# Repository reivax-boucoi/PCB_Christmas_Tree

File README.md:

# PCB_Christmas_Tree
This project is a simple PCB based Christmas ornament with blinky LEDs and rechargeable supercaps.

---
---

### Hardware

---

Project was done in Kicad (yay for open-source !). Project files are here: ```Hardware\Kicad\```, including the custom footprint library ```Hardware\Kicad\christmas_tree.pretty```.

#### Schematic

---

Schematic : ```Hardware\schematic.pdf```

Bill of Materials : ```Hardware\BOM.csv```

Components were chosen based on my current stock. 
* **Power storage**: Instead of traditional batteries, 2 Maxwell 10F 2.7V supercapacitors were used as rechargeable storage, just because I have a bunch of them and don't like non-rechargeable gadgets. Granted, I estimated the tree can only run about 1 hour max per charge (approx. 6mA average current draw), which is not great considering a single CR2032 could probably last several weeks. But, supercaps are fun and you can recharge them with any USB port in <1min.
* **Charging**: An integrated USB connector allows direct charging of the supercaps, through a current limiting resistor. Do not make it less than ~15Ω to not exceed USB spec current capabilities. I added an optional charge balancing circuitry with TL431 shunt Vref, but didn't used it in the end as my caps were quite similar in capacity.
* **Brain of the operations**: I used the ever popular Attiny 25/45/85 series, a small 8-bit AVR micro which offers more than enough capabilities & programming space than I need. Programming port is a TagConnect footprint modified to remove the through holes.
* **LEDs**: Given the limited amount of GPIOs on the µC, I turned to [Charlieplexing](https://en.wikipedia.org/wiki/Charlieplexing), which allows with some clever tricks to drive 12 LEDs with only 4 pins. One thing though, if you want to use different color LEDs you won't be able to adjust their individual brightness easily, so blue LEDs will be dimmer than red by example.
* **Touch button**: For extra fanciness I added a TTP223 touch sensor chip, which allows to cycle between different display modes. The default config works fine even if not populated.

#### Layout

---

To keep this project cheap, the goal was to fit the whole layout on a 10x10cm 2 layer board, which JLCPCB famously offers at 2$ for 5pcs. Decision was made to split the tree in 2 halves that would then be soldered back together, to get a bit extra height. 

For the 1st time I experimented with using the different layers (bare FR4 material, bare copper, copper+soldermask, bare soldermask and silkscreen) to make a somewhat artistic result. For more info on the colors you can get when playing with PCBs I would recommend visiting [this page](https://github.com/Hanqaqa/PCB_Color_Palette).

- Exposed pads spanning the 2 halves of the tree allow to join them and propagate the tracks for the LEDs
- Leds are reverse mounted so they shine through the board: solder mask keepout areas are placed on both sides to let the light through.
- Base of the tree doubles as a USB A port to easily recharge the batteries
- Supercapacitors provide mechanical support to stand the tree upright

<div style="float:left;"> 

</div> 

#### Ordering

---

Zipped gerbers are available (```Hardware\Kicad\gerbers.zip```)to be directly dropped on manufacturers websites like JLCPCB. I used their excellent prototype service for my boards, both cheap and quick.

Feel free to use these files as is or modify and improve the project. Don't forget to share our version as well!

Final dimensions are 88.7mm*98mm.

Ordering settings: 2 layers, 1.6mm board thickness, white silkscreen, HASL(with lead) surface finish, 1oz copper weight, Specify a location for Remove Order Number,

In the Remarks field: "Please note: Some parts use Solder Mask Defined Pads. Do not compensate/modify the solder mask for them. No edge plating required. Center cutout to be routed and discarded."

#### Assembly

---

<div style="float:left;"> 

</div> 
The PCB comes with the 2 halves attached with mousebites. Once separated the remaining burs can be filed off.

Minimum components to be assembled are: C1&C2 supercaps, SW1 power switch, U3 microcontroller, R1 & R10 charging resistors, the 4 220Ω resistors and the LEDs.

To avoid making a custom TagConnect to ICSP adapter, the µC can be programmed in a socket before being soldered on the board.

#### Programming

---

Precompiled version of the firmware: ```Software\main.hex```

To upload using avrdude, run the following commands : `avrdude -u -c usbtiny -p t85 -B 5 -F -U flash:w:main.hex:a -U lfuse:w:0xE2:m -U hfuse:w:0xDF:m -U efuse:w:0xFF:m`

---
---

### Software

---

Software uses Timer1 to cycle between each LED and light it using a 7 bit intensity scale. Several blinking modes can be cycled through with the touch button: fade (default), pixies and debug (one LED at a time)

```Program: TODO bytes (TODO% Full) & Data: TODO bytes (TODO% Full)```

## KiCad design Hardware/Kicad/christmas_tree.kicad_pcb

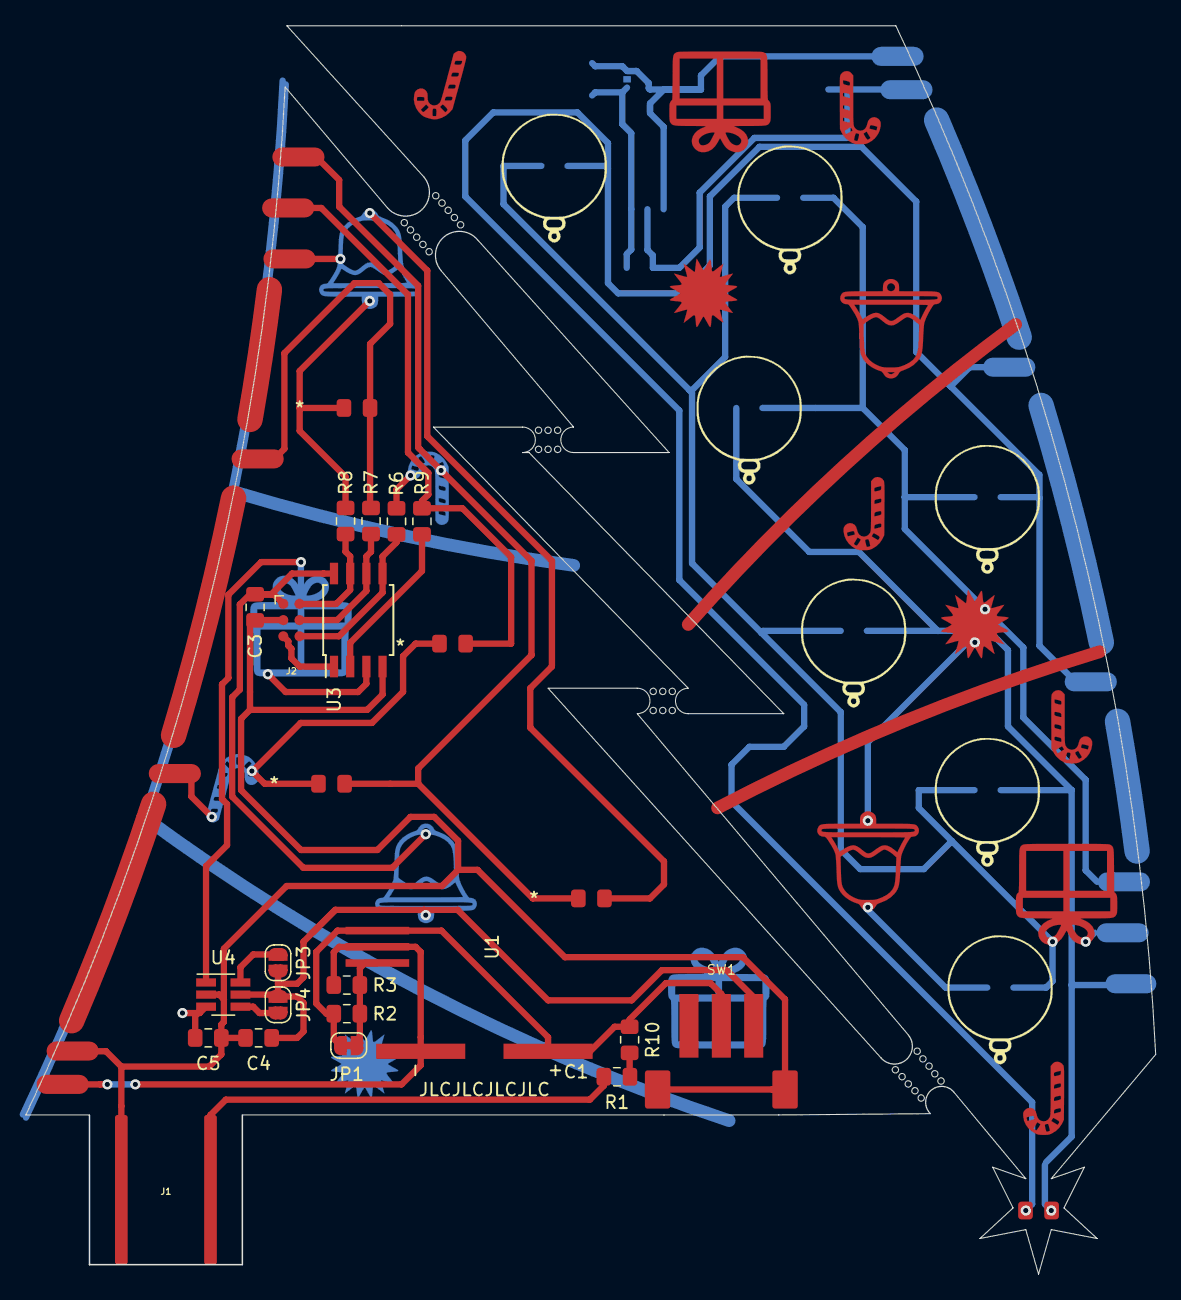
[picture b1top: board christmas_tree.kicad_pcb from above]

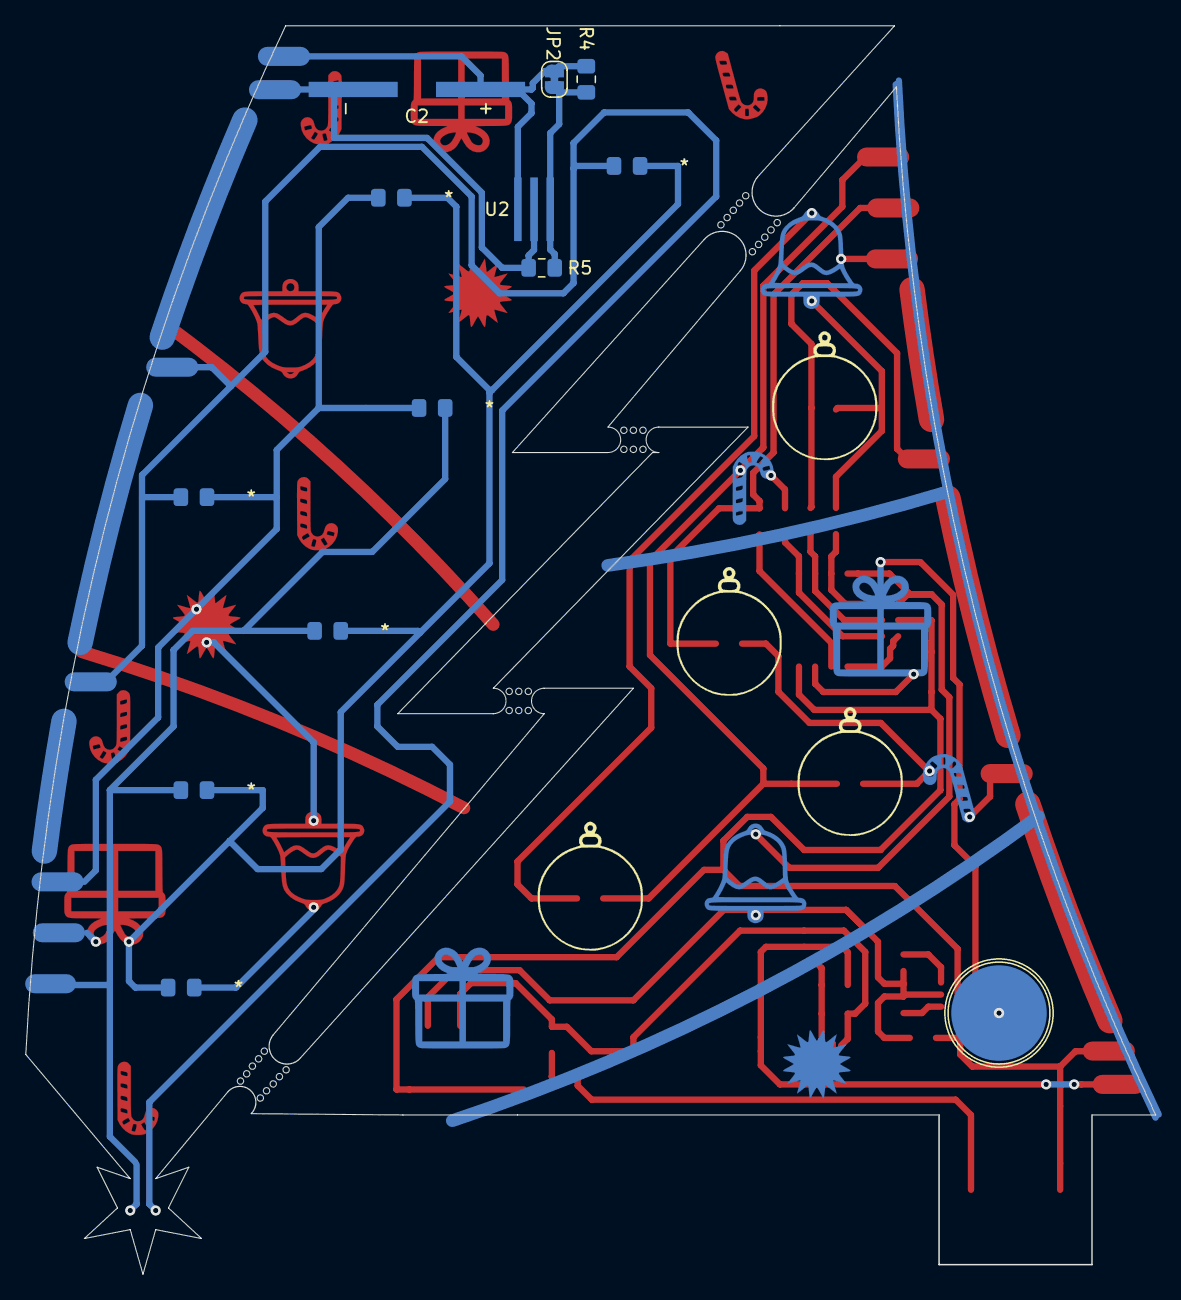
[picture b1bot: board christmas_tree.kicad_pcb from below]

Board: 2 copper layers, 88.7 x 98.0 mm, 43 parts (12 on the bottom side), 21 nets.

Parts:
C1, C2: 10F; Supercap_SMD
C3, C4: 100n; C_0805_2012Metric_Pad1.15x1.40mm_HandSolder
C5: DNP; C_0805_2012Metric_Pad1.15x1.40mm_HandSolder
D1: LED; LED_0805_2012Metric_Pad1.15x1.40mm_HandSolder
D2, D4, D5, D7: LED; LED_0805_orb_r
D3, D6, D8, D9, D10, D11, D12: LED; LED_0805_orb
J1: USB_A; USBA_PCB
J2: Conn_01x06; Tag-Connect_noHoles
J3: Touch; Touch_capacitive
JP1, JP2: Jumper_NC_Small; SolderJumper-2_P1.3mm_Bridged_RoundedPad1.0x1.5mm
JP3, JP4: Jumper_NO_Small; SolderJumper-2_P1.3mm_Open_RoundedPad1.0x1.5mm
R1, R10: 100; R_0805_2012Metric_Pad1.15x1.40mm_HandSolder
R2, R4: 12k; R_0805_2012Metric_Pad1.15x1.40mm_HandSolder
R3, R5: 280k; R_0805_2012Metric_Pad1.15x1.40mm_HandSolder
R6, R7, R8, R9: 220; R_0805_2012Metric_Pad1.15x1.40mm_HandSolder
SW1: SW_SPDT_shield; SPDT_SW_pcb_edge_mount
U1, U2: TL431LP; TO92_H
U3: ATtiny45-20SU; SOIJ-8_5.3x5.3mm_P1.27mm
U4: TTP223; SOT-23-6_Handsoldering
mouse-bite-2mm-slot, mouse-bite-2mm-slot#2: VAL**; mouse-bite-2mm-slot_long
mouse-bite-2mm-slot#3, mouse-bite-2mm-slot#4: VAL**; mouse-bite-2mm-slot

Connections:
+2V5: C1.2, C2.1, JP2.2, R3.2, R4.1, U1.2, U2.3
+BATT: C1.1, JP1.2, R2.1, R10.1, SW1.2, U1.3
/Ahlb: JP4.1, U4.4
/PB0: D1.2, D2.1, D3.1, D4.1, D5.2, D9.2, R6.1
/PB0u: J2.6, R6.2, U3.5
/PB1: D1.1, D2.2, D6.2, D7.1, D8.1, D10.2, R7.1
/PB1u: J2.4, R7.2, U3.6
/PB2: D3.2, D5.1, D6.1, D7.2, D11.2, D12.1, R8.1
/PB2u: J2.2, R8.2, U3.7
/PB3: D4.2, D8.2, D9.1, D10.1, D11.1, D12.2, R9.1
/PB3u: R9.2, U3.2
/RST: J2.5, U3.1
/Tog: JP3.1, U4.6
/Touch: U3.3, U4.1
/Vbus: J1.1, R1.2
GND: C2.2, C3.2, C4.2, C5.2, J1.4, J2.3, R5.2, SW1.4, U2.2, U3.4, U4.2
unnamed: C5.1, J3.1, U4.3
unnamed: JP1.1, R2.2, R3.1, U1.1
unnamed: JP2.1, R4.2, R5.1, U2.1
unnamed: R1.1, R10.2
VCC: C3.1, C4.1, J2.1, JP3.2, JP4.2, SW1.3, U3.8, U4.5

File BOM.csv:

Qty,Reference(s),Value,Footprint,Datasheet
2,"C1, C2",10F,christmas_tree:Supercap_SMD,~
2,"C3, C4",100n,Capacitor_SMD:C_0805_2012Metric_Pad1.15x1.40mm_HandSolder,~
1,C5,DNP,Capacitor_SMD:C_0805_2012Metric_Pad1.15x1.40mm_HandSolder,~
1,D1,LED,LED_SMD:LED_0805_2012Metric_Pad1.15x1.40mm_HandSolder,~
4,"D2, D4, D5, D7",LED,christmas_tree:LED_0805_orb_r,~
7,"D3, D6, D8, D9, D10, D11, D12",LED,christmas_tree:LED_0805_orb,~
1,J1,USB_A,footprints:USBA_PCB, ~
1,J2,Conn_01x06,christmas_tree:Tag-Connect_noHoles,~
1,J3,Touch,christmas_tree:Touch_capacitive,~
2,"JP1, JP2",Jumper_NC_Small,Jumper:SolderJumper-2_P1.3mm_Bridged_RoundedPad1.0x1.5mm,~
2,"JP3, JP4",Jumper_NO_Small,Jumper:SolderJumper-2_P1.3mm_Open_RoundedPad1.0x1.5mm,~
2,"R1, R10",100,Resistor_SMD:R_0805_2012Metric_Pad1.15x1.40mm_HandSolder,~
2,"R2, R4",12k,Resistor_SMD:R_0805_2012Metric_Pad1.15x1.40mm_HandSolder,~
2,"R3, R5",280k,Resistor_SMD:R_0805_2012Metric_Pad1.15x1.40mm_HandSolder,~
4,"R6, R7, R8, R9",220,Resistor_SMD:R_0805_2012Metric_Pad1.15x1.40mm_HandSolder,~
1,SW1,SW_SPDT_shield,footprints:SPDT_SW_pcb_edge_mount,~
2,"U1, U2",TL431LP,christmas_tree:TO92_H,http://www.ti.com/lit/ds/symlink/tl431.pdf
1,U3,ATtiny45-20SU,Package_SO:SOIJ-8_5.3x5.3mm_P1.27mm,http://ww1.microchip.com/downloads/en/DeviceDoc/atmel-2586-a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
1,U4,TTP223,Package_TO_SOT_SMD:SOT-23-6_Handsoldering,https://datasheet.lcsc.com/szlcsc/TTP223-BA6_C80757.pdf

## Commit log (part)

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2021-08-04 added code
2021-11-06 added img
2021-11-08 added schematic
2021-11-16 added zipped Gerbers
2021-11-29 added led polarity on DWG.user layer
2021-11-30 added prog
2021-12-08 added pic
